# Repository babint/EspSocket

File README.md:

# EspSocket
KiCad Project for creating a PCB for the DIY ESP-12 Socket Project

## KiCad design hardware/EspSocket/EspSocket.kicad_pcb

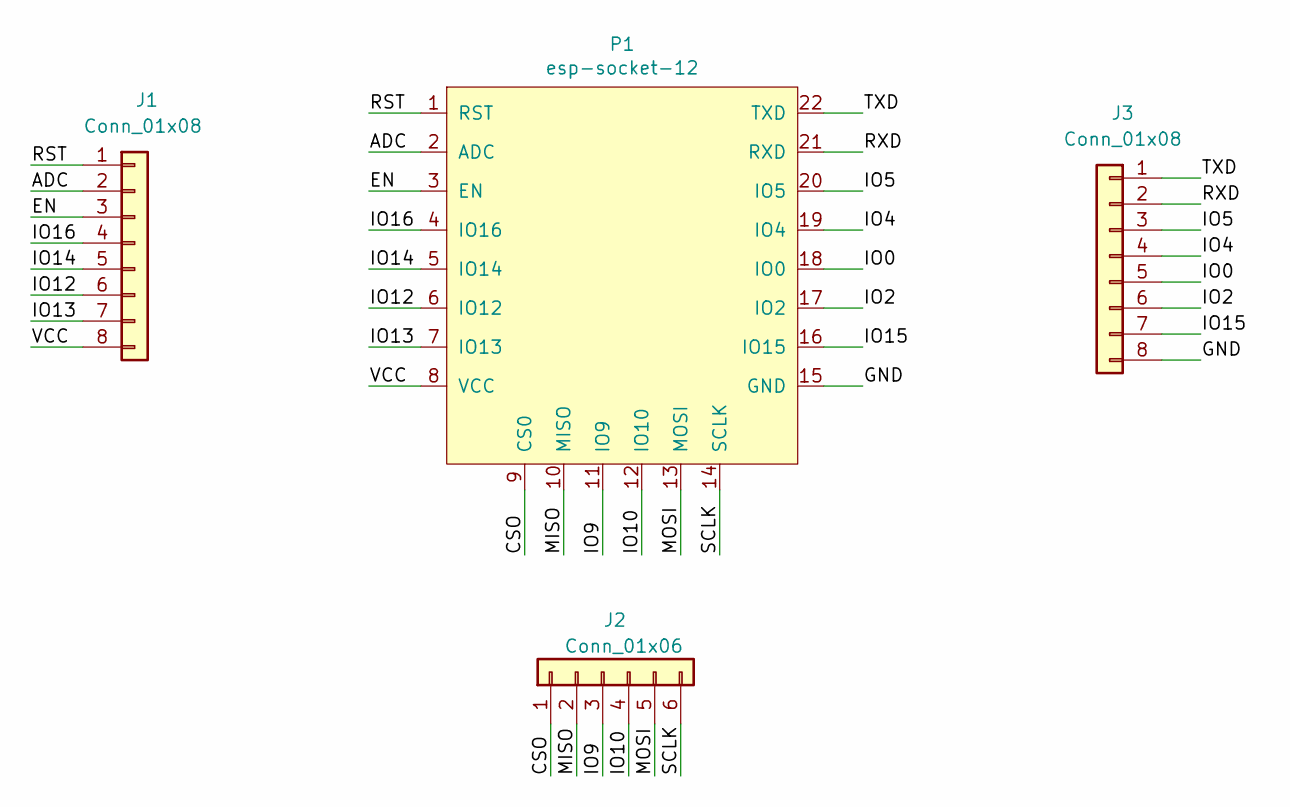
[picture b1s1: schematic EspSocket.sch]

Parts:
J1, J3: Conn_01x08; PinSocket_1x08_P2.54mm_Vertical
J2: Conn_01x06; PinSocket_1x06_P2.54mm_Vertical
P1: esp-socket-12

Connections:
/ADC: J1.2, P1.2 (ADC)
/CSO: J2.1, P1.9 (CS0)
/EN: J1.3, P1.3 (EN)
/GND: J3.8, P1.15 (GND)
/IO0: J3.5, P1.18 (IO0)
/IO2: J3.6, P1.17 (IO2)
/IO4: J3.4, P1.19 (IO4)
/IO5: J3.3, P1.20 (IO5)
/IO9: J2.3, P1.11 (IO9)
/IO10: J2.4, P1.12 (IO10)
/IO12: J1.6, P1.6 (IO12)
/IO13: J1.7, P1.7 (IO13)
/IO14: J1.5, P1.5 (IO14)
/IO15: J3.7, P1.16 (IO15)
/IO16: J1.4, P1.4 (IO16)
/MISO: J2.2, P1.10 (MISO)
/MOSI: J2.5, P1.13 (MOSI)
/RST: J1.1, P1.1 (RST)
/RXD: J3.2, P1.21 (RXD)
/SCLK: J2.6, P1.14 (SCLK)
/TXD: J3.1, P1.22 (TXD)
/VCC: J1.8, P1.8 (VCC)

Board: 2 copper layers, 5 parts (1 on the bottom side), 22 nets, no tracks yet.

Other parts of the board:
GRef: LOGO; drpep_F_Mask

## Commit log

2021-01-06 KiCad Project Init
2021-01-06 Add pepper logo
2021-01-06 Adding Schematic with socket + jumpers
2021-01-06 Assign Footprints
2021-01-06 Create board from netlist
2021-01-06 Try adding some artwork
2021-01-06 move art up
